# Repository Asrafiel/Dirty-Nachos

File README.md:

# Dirty-Nachos
Really Dirty VCF

EuroRack Module

# CURRENT VERSION 0.2 !!UNTESTED, BEWARE!!

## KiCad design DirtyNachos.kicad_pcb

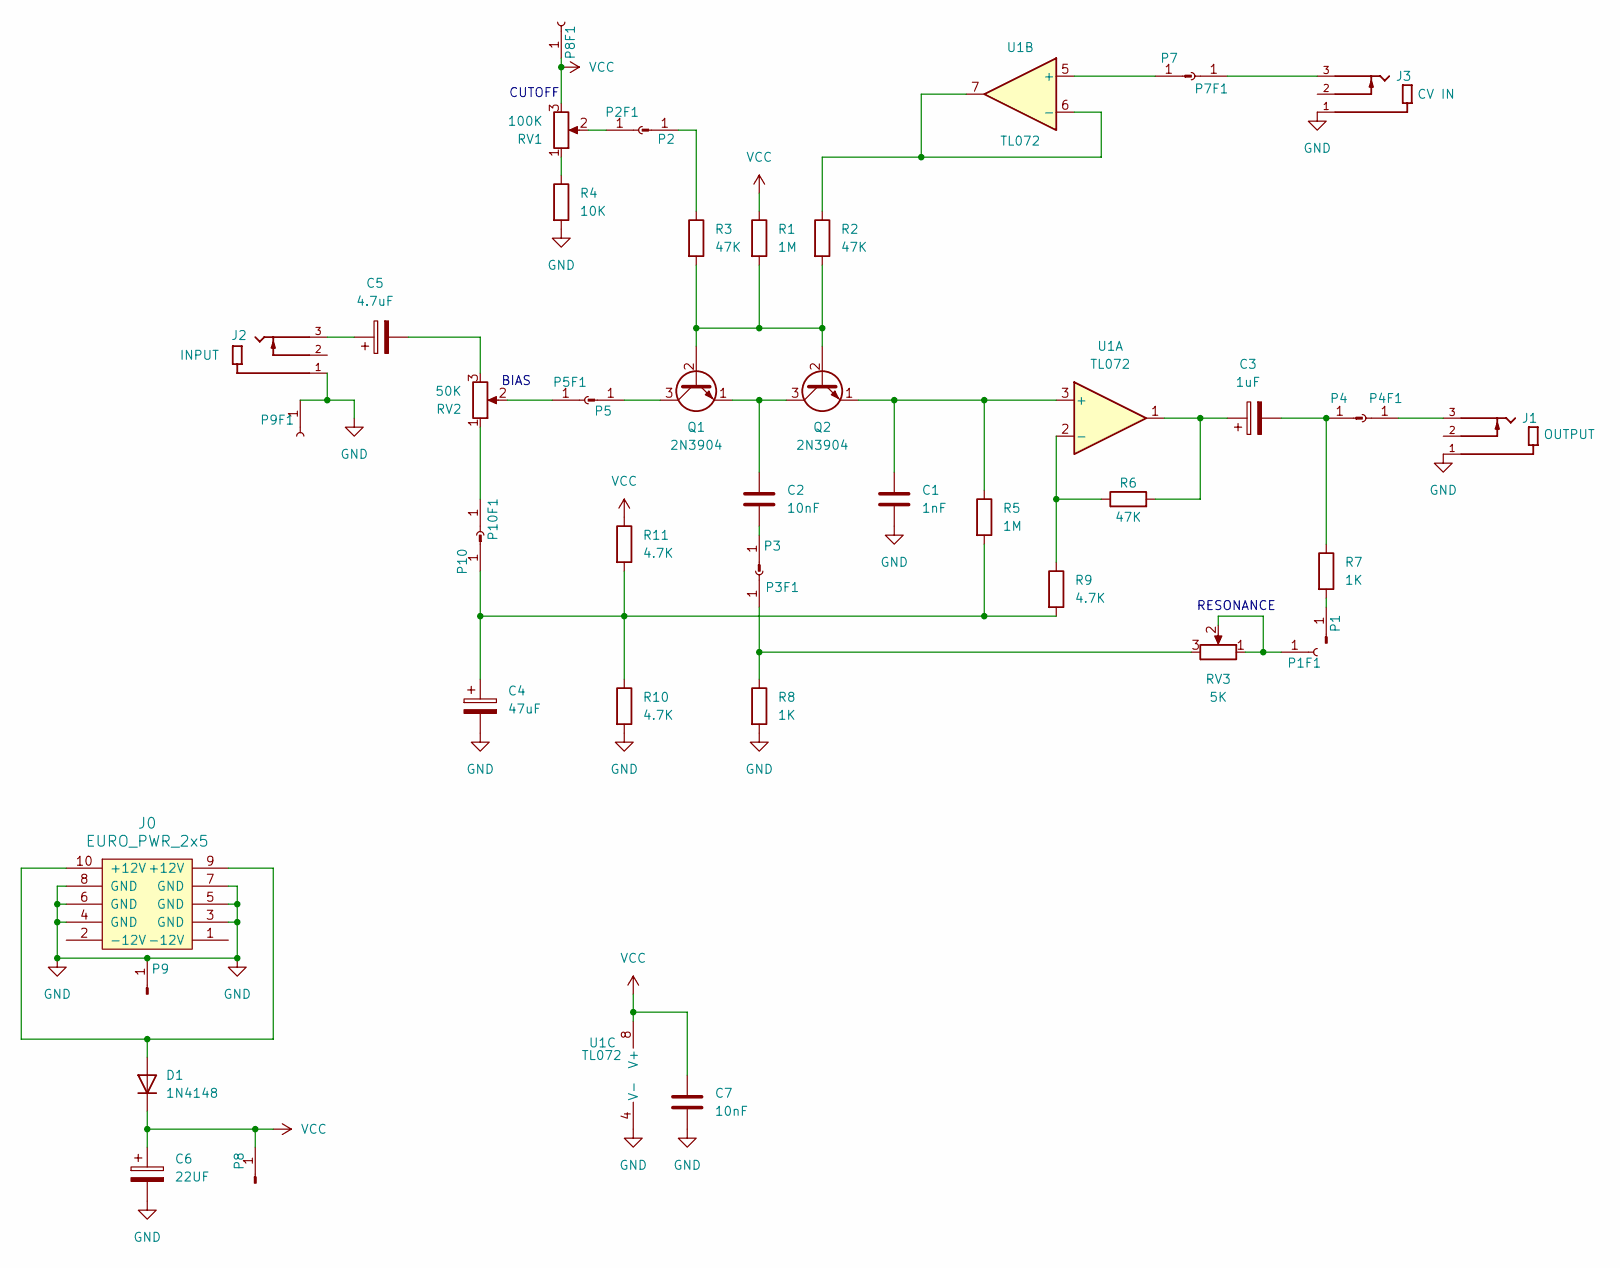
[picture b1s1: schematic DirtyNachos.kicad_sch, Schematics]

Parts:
C1: 1nF; C_Rect_L7.2mm_W2.5mm_P5.00mm_FKS2_FKP2_MKS2_MKP2
C2: 10nF; C_Rect_L7.2mm_W2.5mm_P5.00mm_FKS2_FKP2_MKS2_MKP2
C3: 1uF; C_Rect_L7.2mm_W2.5mm_P5.00mm_FKS2_FKP2_MKS2_MKP2
C4: 47uF; C_Rect_L7.2mm_W2.5mm_P5.00mm_FKS2_FKP2_MKS2_MKP2
C5: 4.7uF; CP_Radial_D5.0mm_P2.50mm
C6: 22UF; CP_Radial_D5.0mm_P2.50mm
C7: 10nF; CP_Radial_D5.0mm_P2.50mm
D1: 1N4148; D_DO-35_SOD27_P7.62mm_Horizontal
J0: EURO_PWR_2x5; IDC-Header_2x05_P2.54mm_Vertical
J1: OUTPUT; Jack_3.5mm_QingPu_WQP-PJ398SM_Vertical_CircularHoles; PARTREV 1
J2: INPUT; Jack_3.5mm_QingPu_WQP-PJ398SM_Vertical_CircularHoles; PARTREV 1
J3: CV IN; Jack_3.5mm_QingPu_WQP-PJ398SM_Vertical_CircularHoles; PARTREV 1
P1, P2, P3, P4, P5, P7, P8, P9, P10: Conn_01x01_Pin; PinHeader_1x01_P2.54mm_Vertical
P1F1, P2F1, P3F1, P4F1, P5F1, P7F1, P8F1, P9F1, P10F1: Conn_01x01_Socket; PinSocket_1x01_P2.54mm_Vertical
Q1, Q2: 2N3904; TO-92_Inline
R1, R5: 1M; R_Axial_DIN0207_L6.3mm_D2.5mm_P10.16mm_Horizontal
R2, R3, R6: 47K; R_Axial_DIN0207_L6.3mm_D2.5mm_P10.16mm_Horizontal
R4: 10K; R_Axial_DIN0207_L6.3mm_D2.5mm_P10.16mm_Horizontal
R7, R8: 1K; R_Axial_DIN0207_L6.3mm_D2.5mm_P10.16mm_Horizontal
R9, R10, R11: 4.7K; R_Axial_DIN0207_L6.3mm_D2.5mm_P10.16mm_Horizontal
RV1: 100K; Potentiometer_Alps_RK09K_Single_Vertical
RV2: 50K; Potentiometer_Alps_RK09K_Single_Vertical
RV3: 5K; Potentiometer_Alps_RK09K_Single_Vertical
U1: TL072; DIP-8_W7.62mm_Socket

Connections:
GND: C1.2, C4.2, C6.2, C7.2, J0.3 (GND), J0.4 (GND), J0.5 (GND), J0.6 (GND), J0.7 (GND), J0.8 (GND), J1.1, J2.1, J3.1, P9.1, P9F1.1, R4.2, R8.2, R10.2, U1.4 (V-); also elsewhere on the board
unnamed 1: C3.1, R6.2, U1.1; also elsewhere on the board
unnamed: C5.1, J2.3
unnamed: C5.2, RV2.3
unnamed: D1.2 (A), J0.9 (+12V), J0.10 (+12V)
unnamed: P1.1, R7.2
unnamed: P1F1.1, RV3.1, RV3.2
unnamed: P2.1, R3.1
unnamed: P2F1.1, RV1.2
unnamed: C2.2, P3.1
unnamed: P3F1.1, R8.1, RV3.3
unnamed: C3.2, P4.1, R7.1
unnamed: J1.3, P4F1.1
unnamed: P5.1, Q1.3 (C)
unnamed: P5F1.1, RV2.2
unnamed 15: P7.1, U1.5 (+); also elsewhere on the board
unnamed: J3.3, P7F1.1
unnamed: C4.1, P10.1, R5.2, R9.2, R10.1, R11.2
unnamed: P10F1.1, RV2.1
unnamed: Q1.2 (B), Q2.2 (B), R1.2, R2.2, R3.2
unnamed: C2.1, Q1.1 (E), Q2.3 (C)
unnamed 21: C1.1, Q2.1 (E), R5.1, U1.3 (+); also elsewhere on the board
unnamed: R4.1, RV1.1
unnamed 23: R6.1, R9.1, U1.2 (-); also elsewhere on the board
unnamed 24: R2.1, U1.6 (-), U1.7; also elsewhere on the board
VCC: C6.1, C7.1, D1.1 (K), P8.1, P8F1.1, R1.1, R11.1, RV1.3, U1.8 (V+); also elsewhere on the board

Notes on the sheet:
BIAS
CUTOFF
RESONANCE

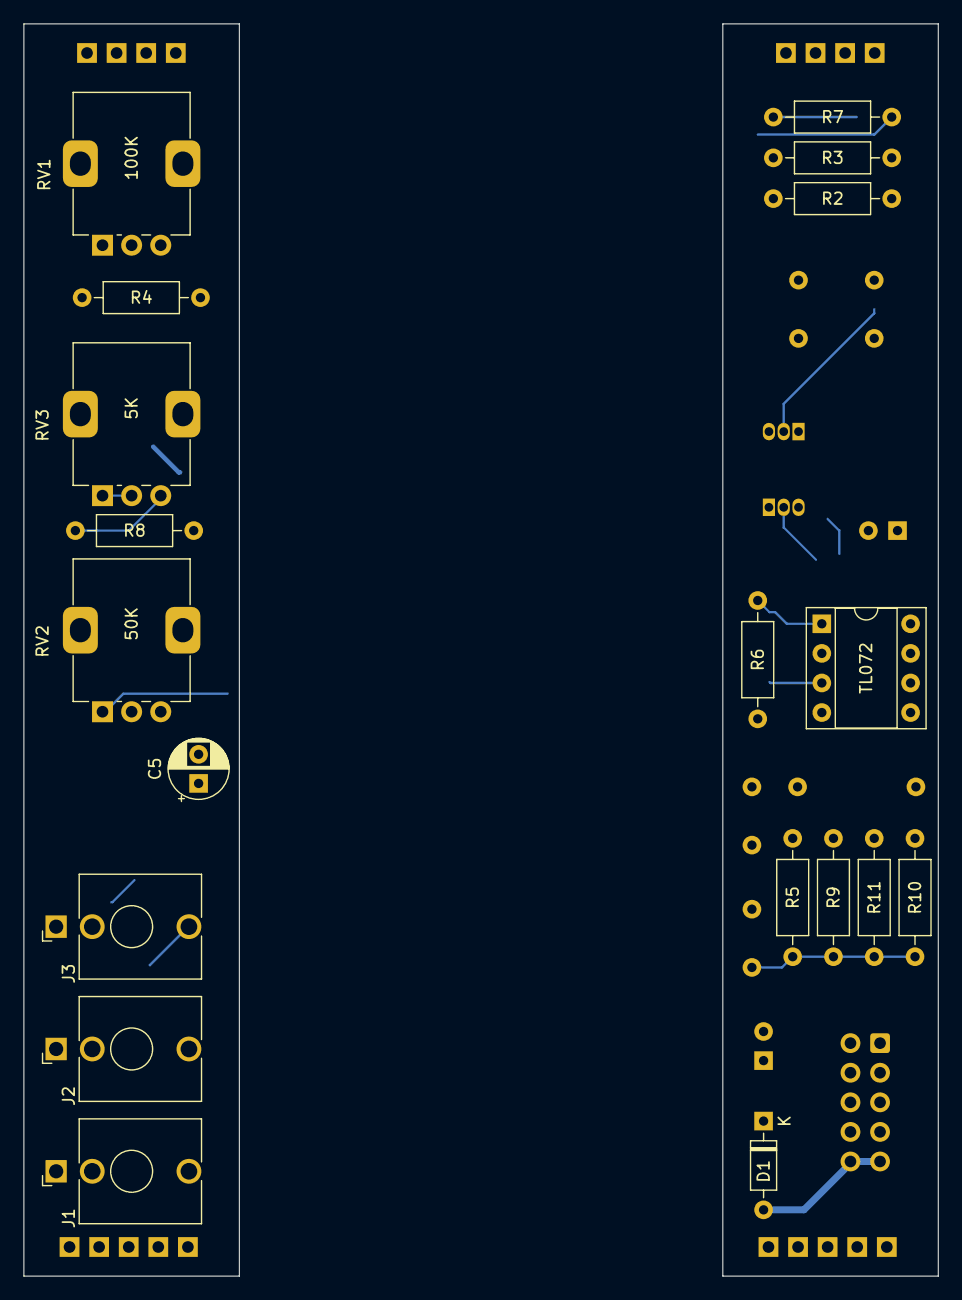
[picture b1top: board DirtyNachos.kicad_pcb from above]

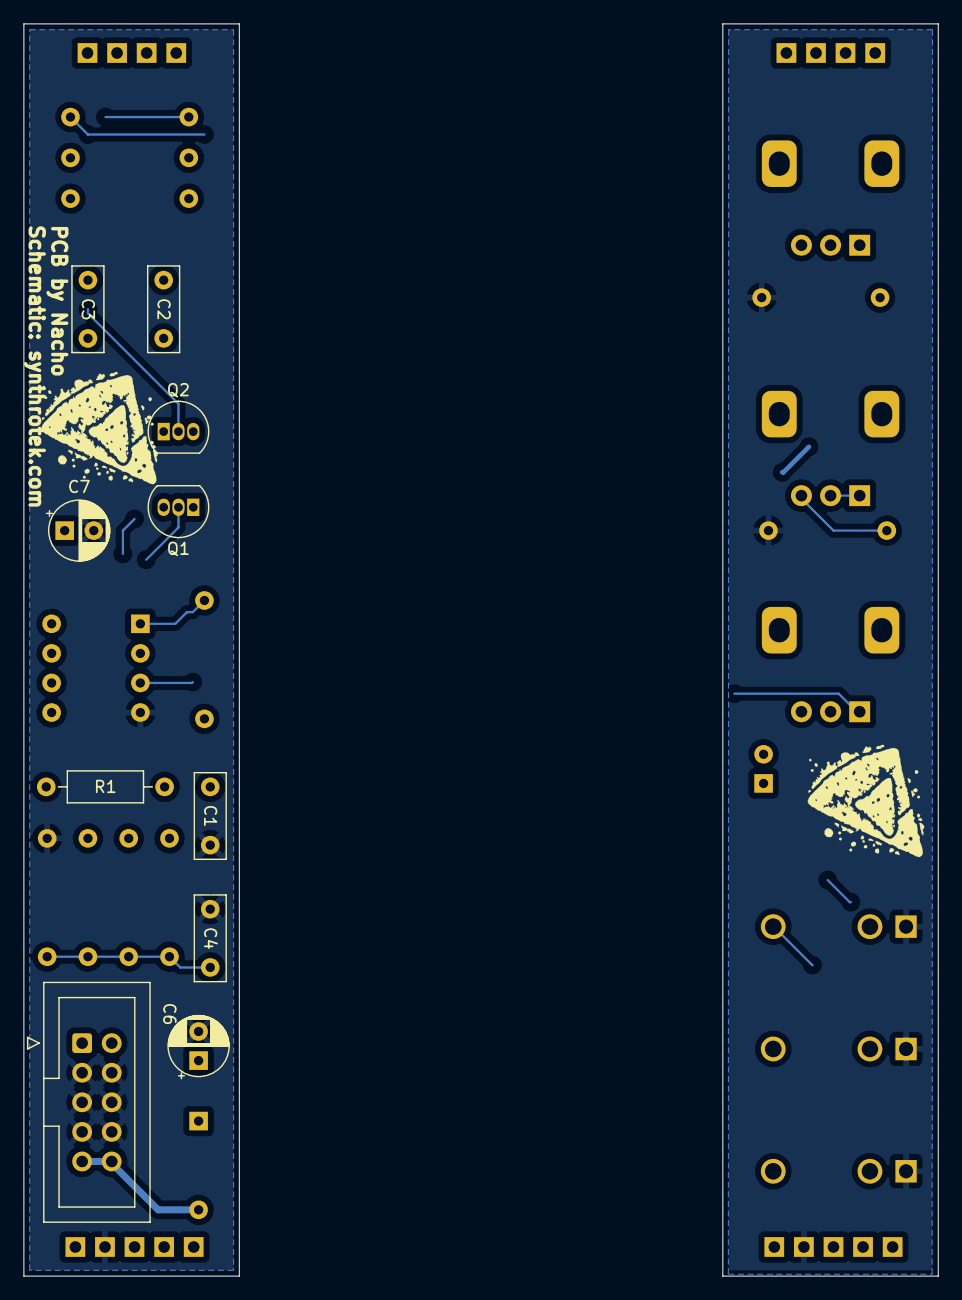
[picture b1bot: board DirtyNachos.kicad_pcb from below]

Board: 2 copper layers, 78.5 x 107.5 mm, 49 parts (19 on the bottom side), 26 nets.

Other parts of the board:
Ref**: Val**; DirtNacho
Ref**#2: Val**; DirtNacho
TL072: TL072; DIP-8_W7.62mm_Socket

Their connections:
GND: TL072.4 (V-); also elsewhere on the board
unnamed 1: TL072.1; also elsewhere on the board
unnamed 15: TL072.5 (+); also elsewhere on the board
unnamed 21: TL072.3 (+); also elsewhere on the board
unnamed 23: TL072.2 (-); also elsewhere on the board
unnamed 24: TL072.6 (-), TL072.7; also elsewhere on the board
VCC: TL072.8 (V+); also elsewhere on the board

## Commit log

2024-09-09 v0.1
    v0.1
2024-09-09 Updates v0.2
    Better Faceplate.
    New holes now with copper.
2024-09-10 V0.2
    Fixed Tracks. Now they are wider. And optimized routes.
2024-09-10 V0.2
    More updates better paths ensuring aligment.
2024-09-10 Delete Gerber/PLATE directory
    Removed unnecessary files.
2024-09-10 V0.2
    New gerbers for V0.2
2024-09-10 Delete DirtyNachos-Backup.kicad_pro
    Removed Backup files
2024-09-24 Small updates.
